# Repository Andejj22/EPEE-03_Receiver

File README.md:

# EPEE-03_Receiver
Repo for project work KiCad files

## How to start working on this repo
First make sure you have git installed on your computer. For Windows OS it's probably easies to download "Git for Windows" and configure it according to the instructions. Linux shouls have git preinstalled and ready to work. After you have git ready and working, go to the directory you want to have your copy of the project in, and type
```
git clone https://github.com/Andejj22/EPEE-03_Receiver.git
```
When actually typing these leave out the brackets. Now you should have a local copy of this project. To start working, create a new branch and switch to it with
```
git checkout -b [your_new_branch_name]
```
And you're ready to work! It's good practice to name the branch after the feature you're working on. After you've done your work, it's time to commit and push the changes. Start by typing
```
git add .
```
This adds all the modifications to the list of things to commit. Then, you can commit the changes to the local branch by typing
```
git commit -m "your_commit_message"
```
Again, it's good practice to name what you've done within this commit. After committing, you can push the changes to the remote repository by
```
git push origin [your_branch_name]
```
This will create a new branch for this remote repository. After reviewing the changes, a pull request can be made to merge the changes to the master branch. 

Remember that this whole thing needs to be done for the first time only. After that, simply pulling the changes from the remote repository is enough when starting the work. This ensures that there will be no mis-match when merging the changes to the master branch. This can be done with 
```
git pull origin [branch_name]
```

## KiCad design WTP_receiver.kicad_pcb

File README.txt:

<<<<<<<<<<<This is an example of a README File>>>>>>>>>>>>>>

<Responsible>
Antti Jormanainen

<Short WP description>
WP4 is designing the PCB layout based on schematics formed in WP2 and simulated in WP3 and coil specifications calculated in WP1.

<File description>
This WP folder may contain some version of the PCB layout files, but the most updated versions are held in GitHub repository available in: https://github.com/Andejj22/EPEE-03_Receiver (private)

You can add your GitHub usernames here in this file and I will grant you access. If urgent need for access message me via Telegram.

<Version info> (Optional and not needed in most cases)

30.1.2024 Setting up the repository, start of the PCB layout design by adding edge cuts to 54x86 mm dimensions, reserved space for coils, some silkscreens added. Related commit: 05e9e05

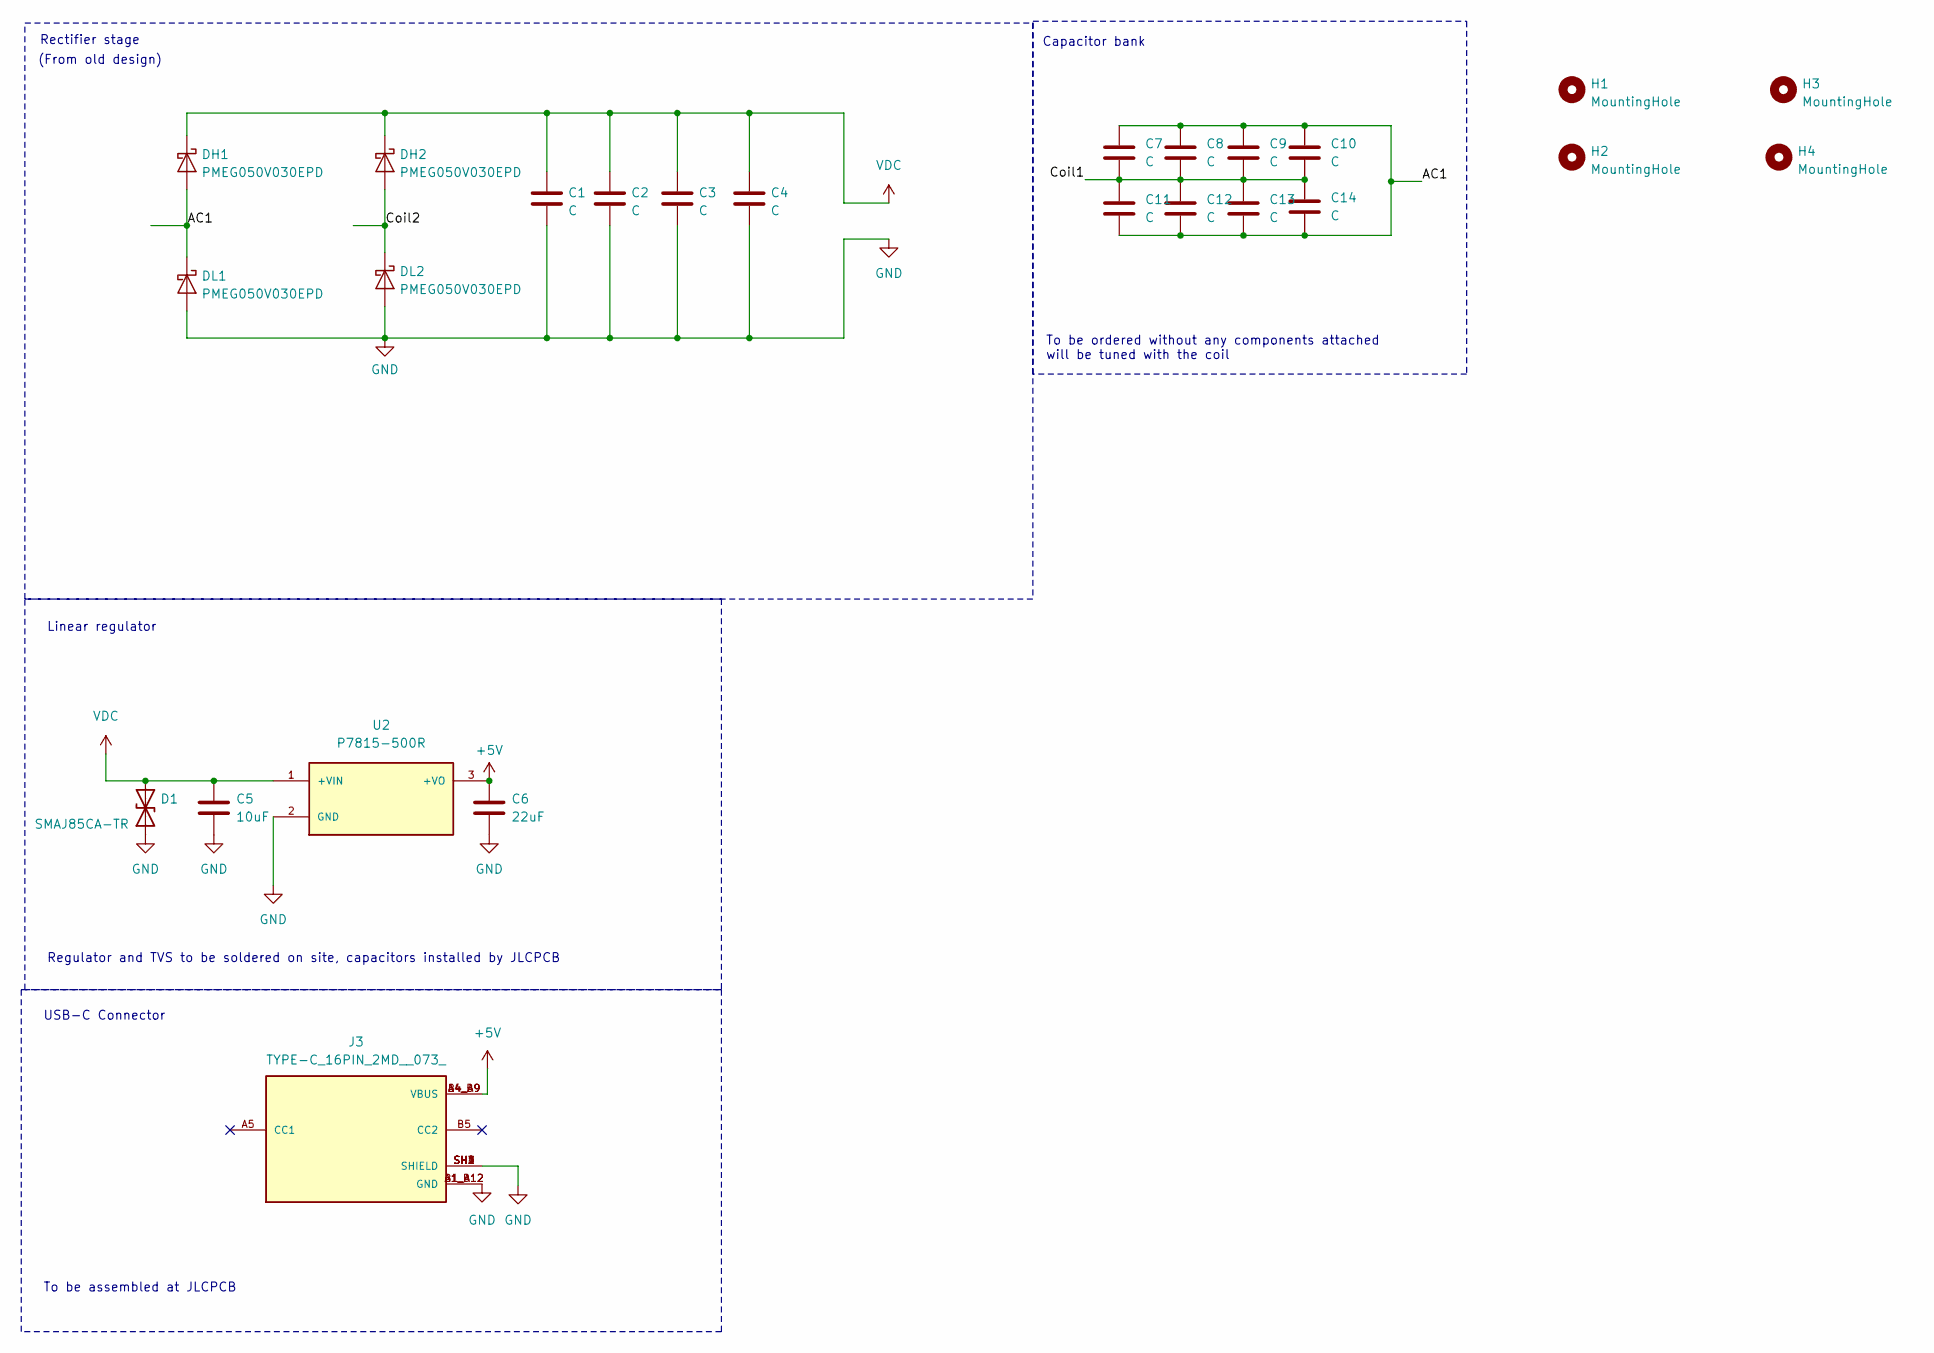
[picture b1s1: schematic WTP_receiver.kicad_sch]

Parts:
C1, C2, C4: C; C_0805_2012Metric; JLCPCB BOM 0
C3: C; C_1210_3225Metric; JLCPCB BOM 0
C5: 10uF; C_2220_5650Metric; LCSC Part C153035
C6: 22uF; C_0805_2012Metric; LCSC Part C5137600
C7, C8, C9, C10, C11, C12, C13, C14: C; C_1111_2828_metric; JLCPCB BOM 0
D1: SMAJ85CA-TR; D_SMA; JLCPCB BOM 0
DH1, DH2: PMEG050V030EPD; Nexperia_CFP15_SOT-1289; JLCPCB BOM 0
DL1, DL2: PMEG050V030EPD; Nexperia_CFP15_SOT-1289; JLCPCB BOM 0
H1, H2, H3, H4: MountingHole; MountingHole_3.2mm_M3; JLCPCB BOM 0
J3: TYPE-C_16PIN_2MD__073_; SHOUHAN_TYPE-C_16PIN_2MD__073_; PARTREV A; LCSC Part C668624
U2: P7815-500R; CONV_P7815-500R; PARTREV 1.0; JLCPCB BOM 0

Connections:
+5V: C6.1, J3.A4_B9 (VBUS), J3.B4_A9 (VBUS), U2.3 (+VO)
/AC1: C7.1, C8.1, C9.1, C10.1, C11.2, C12.2, C13.2, C14.2, DH1.1 (A), DH1.2 (A), DL1.3 (K)
/Coil1: C7.2, C8.2, C9.2, C10.2, C11.1, C12.1, C13.1, C14.1
/Coil2: DH2.1 (A), DH2.2 (A), DL2.3 (K)
GND: C1.2, C2.2, C3.2, C4.2, C5.2, C6.2, D1.1 (A1), DL1.1 (A), DL1.2 (A), DL2.1 (A), DL2.2 (A), J3.A1_B12 (GND), J3.B1_A12 (GND), J3.SH1 (SHIELD), J3.SH2 (SHIELD), J3.SH3 (SHIELD), J3.SH4 (SHIELD), U2.2 (GND)
VDC: C1.1, C2.1, C3.1, C4.1, C5.1, D1.2 (A2), DH1.3 (K), DH2.3 (K), U2.1 (+VIN)

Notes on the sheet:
Capacitor bank
Linear regulator
USB-C Connector
To be assembled at JLCPCB
Rectifier stage
Regulator and TVS to be soldered on site, capacitors installed by JLCPCB
To be ordered without any components attached will be tuned with the coil
(From old design)

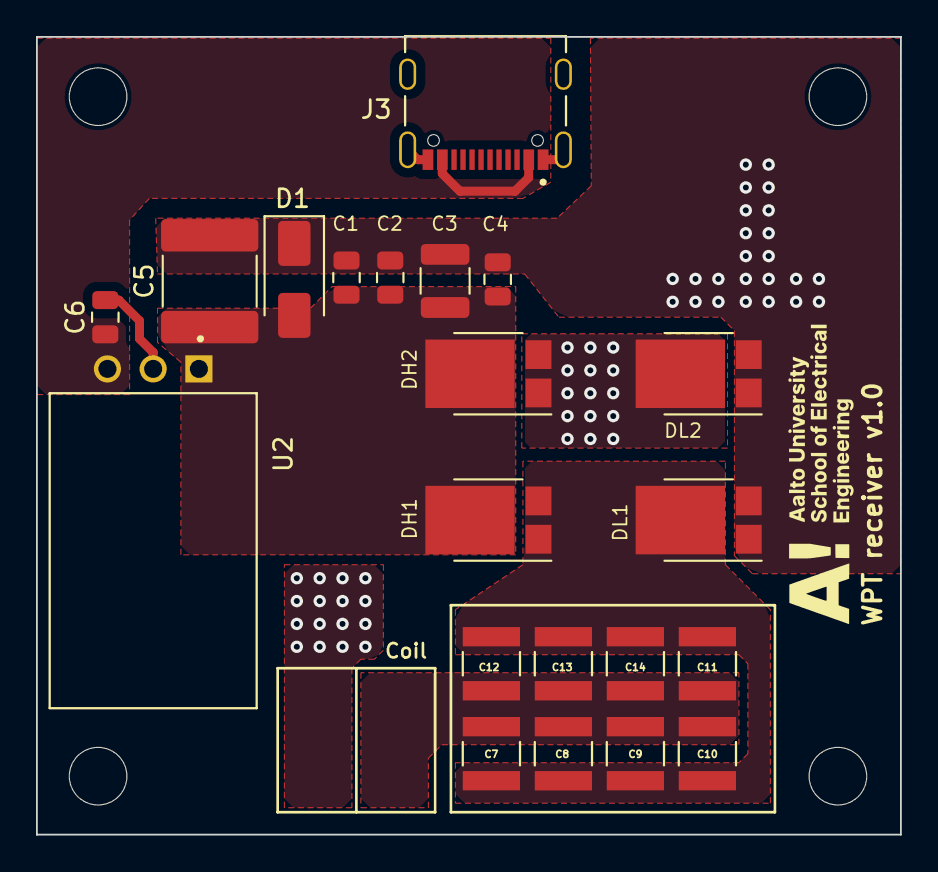
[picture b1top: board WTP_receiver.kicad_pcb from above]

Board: 2 copper layers, 48.0 x 44.3 mm, 25 parts (0 on the bottom side), 6 nets.

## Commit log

2024-02-05 add coil with 44 turns, 0.7mm trace and 10mil spacing for measure
2024-02-08 Create LICENSE
2024-02-08 add rectifier circuit to schematic and PCB from old files
2024-02-08 deleted extra readme file
2024-02-13 initial version with traces and components
2024-02-25 improvements done according to what was agreed in the project meeting
2024-02-26 generate gerbers, start working with BOM
2024-02-26 update BOM and gerbers
